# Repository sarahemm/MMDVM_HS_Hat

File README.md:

# MMDVM_HS_Hat
MMDVM_HS Hat for the Raspberry Pi (Zero)

This project provides a Raspberry Pi Hat for the [MMDVM_HS Hotspot](https://github.com/juribeparada/MMDVM_HS). It was designed for the Raspberry Pi Zero, but should work on any other Pi with the Hat interface. 

First revisions of the board have been built successfully!

The PCB is designed in KiCad and the necessary libraries are included. The supplied Gerber files can be used to order PCBs, for example at Elecrow or DirtyPCBs. The board's dimensions are 65x30mm.

You can order 3 beautiful, purple Revision 1.2 PCBs for $15 at [OSHPark](https://oshpark.com/shared_projects/WaiMw5XE)! 

## 3D printed Case

Thanks to Toufik, F0DEI we added the sources for a shiny case that you can print with your 3D printer. It may require a little upscaling depending on your printer model. It can carry a Raspberry Pi Zero (W) with MMDVM_HS_Hat (SMA) on top.

## Revisions
### Revision 0
This was the first released version that still contains a couple of errors. There is a trace missing between L1 and C1 that needs to be fixed with a small blob of solder or magnet wire. Otherwise the RF connector is not connected to the ADF7021. The GND side of C20 and C22 is not connected to the rest of the board's GND, this needs to be fixed with a little wire to any other GND. CE is connected directly to +3.3V which disallows mode scanning to work. If you just use one mode this is fine, otherwise the connection to the CE pin has to be cut and connected to PC14 on the STM32.

Earlier schematics showed C14 as 1uF. This is wrong and needs to be replaced with 1nF, otherwise the ADF7021 will neither receive nor transmit properly.

With these changes, you can build a fully working MMDVM_HS with the old revision 0 boards

### Revision 1
These boards have "Revision 1" written on them. All bugs found in revision 0 are fixed in this version. Apart from that, the STM32's BOOT0 and RESET pins are connected to GPIOs of the Raspberry Pi. This way, flashing should be possible without manually jumpering BOOT0 and triggering a reset.

Component placement did not change between revisions 0 and 1, therefore any stencils for revision 0 should work for revision 1 boards, too.

### Revision 1.1
Rewired 3v3 line for Nextion display connector to 5v0. Added SERVICE LED for visual heartbeat. Fixed improper labelling on P25 and YSF LEDs. Due to added LEDs this revision requires a new stencil.

### Revision 1.2
This Revision adds support for an optional AN1603-443 ceramic antenna. Insert C27 or C28, depending on what kind of antenna you want to use.

### Revision 1.3
The boot jumper was removed and the STlink header moved to its position. This gave space for another 4-pin header allowing to connect I²C OLED displays. No new stencil needed

### Revision 1.4
The SVC LED has been rotated and thus aligned to the layout of all other LEDs. The RainSun ceramic antenna has been replaced by a model that can be ordered at Mouser. DC line filtering has been added to 3v3 line.

### Revision 1.5
A fith mode LED has been added to the board to show NXDN activity. The two pin headers moved downwards a little. The rev1.4 stencil can be re-used if you manually add solder paste to R19 and D9 afterwards.

### Revision 1.6
Inner RX/TX pins of Nextion connector have been swapped. External VCO inductor L6 was added. This is optional for VHF use. D-Star and DMR LEDs were swapped to flash LEDs in proper scan order :).

### Revision 1.6a - sen
Updated for KiCad 9 footprints, as well as some silkscreen changes. No BOM changes, so standard 1.6 BOM applies.Previous versions of stencils won't work well with this one due to footprint shapes changing and some slight component location nudges.

## BOM
* All necessary parts for the Revision 1.1 board can be ordered at Mouser using the following [shopping cart](http://www.mouser.com/ProjectManager/ProjectDetail.aspx?AccessID=780b8eac44)
* All necessary parts for the Revision 1.2 board can be ordered at Mouser using the following [shopping cart](http://www.mouser.com/ProjectManager/ProjectDetail.aspx?AccessID=035e777242)
* There is also a light version of revision 1.2 without the reset switch, 2.54mm headers and SMA connector [Link](http://www.mouser.com/ProjectManager/ProjectDetail.aspx?AccessID=3f7d0256e1)
* The parts for Revision 1.3 board are in this [Mouser cart](http://www.mouser.com/ProjectManager/ProjectDetail.aspx?AccessID=250d76339b) and the light version is [here](http://www.mouser.com/ProjectManager/ProjectDetail.aspx?AccessID=2d533ac53d)
* [Mouser project](http://www.mouser.com/ProjectManager/ProjectDetail.aspx?AccessID=5cab954f40) for MMDVM_HS_Hat revision 1.4
* There is another [Mouser cart for rev 1.5](https://www.mouser.com/ProjectManager/ProjectDetail.aspx?AccessID=5a3e4ae018).
* And this is the [rev1.6 cart](https://www.mouser.com/ProjectManager/ProjectDetail.aspx?AccessID=48302f4221) and its [light version](https://www.mouser.com/ProjectManager/ProjectDetail.aspx?AccessID=ac888de33a).

Please note that the onboard ceramic antenna is not supplied by Mouser and therefore missing in the carts for revisions up to 1.3.

Either the ADF7021 or the ADF7021-N can be used. Define the proper version in the firmware!

## Firmware Installation

### Compile and upload manually

For specific details about the firmware installation, check [these](https://github.com/juribeparada/MMDVM_HS#build-de-firmware-and-upload-to-zumspot-rpi) instructions. The process is similar to the installation on the ZumSpot Pi. 

Enable the following settings in Config.h:

    #define MMDVM_HS_HAT_REV12
    #define ENABLE_ADF7021
    #define ADF7021_14_7456
    #define STM32_USART1_HOST
    #define ENABLE_SCAN_MODE

Build the firmware:

    make

And finally upload the firmware to the MMDVM_HS_Hat:

    sudo make mmdvm_hs_hat

### Update within Pi-Star

Andy, MW0MWZ was so kind as to add a script which allows for updating the firmware of the MMDVM_HS_Hat within the running Pi-Star system. It uses the pre-compiled binaries from Andy's (CA6JAU) github repository. The update can be done with:

```
$ pistar-zumspotflash hs_hat
```

on the command line.

## Accessoires

* A case for the #MMDVM_HS_Hat can be found at amazon: [Case](https://www.amazon.de/Hochwertiges-schwarzes-auml-uuml-Raspberry/dp/B01FHDXNNU)

* An OLED display also to be found at amazon: [Display](https://www.amazon.de/dp/B01M9JVYIS/ref=cm_sw_r_wa_api_RmZ9zb01APZTV)

## License
This project is released under the Creative Commons Attribution-NonCommercial-ShareAlike 3.0 (CC-BY-NC-SA 3.0, https://creativecommons.org/licenses/by-nc-sa/3.0/) license. You may edit and share it as you like, as long as credit is given and the license is not changed. You can build as many boards for you and your friends as you like and you can even sell it to them to cover your costs, **however it is strictly forbidden to turn this into a commercial product! You are not allowed to build and sell these boards for profit!**

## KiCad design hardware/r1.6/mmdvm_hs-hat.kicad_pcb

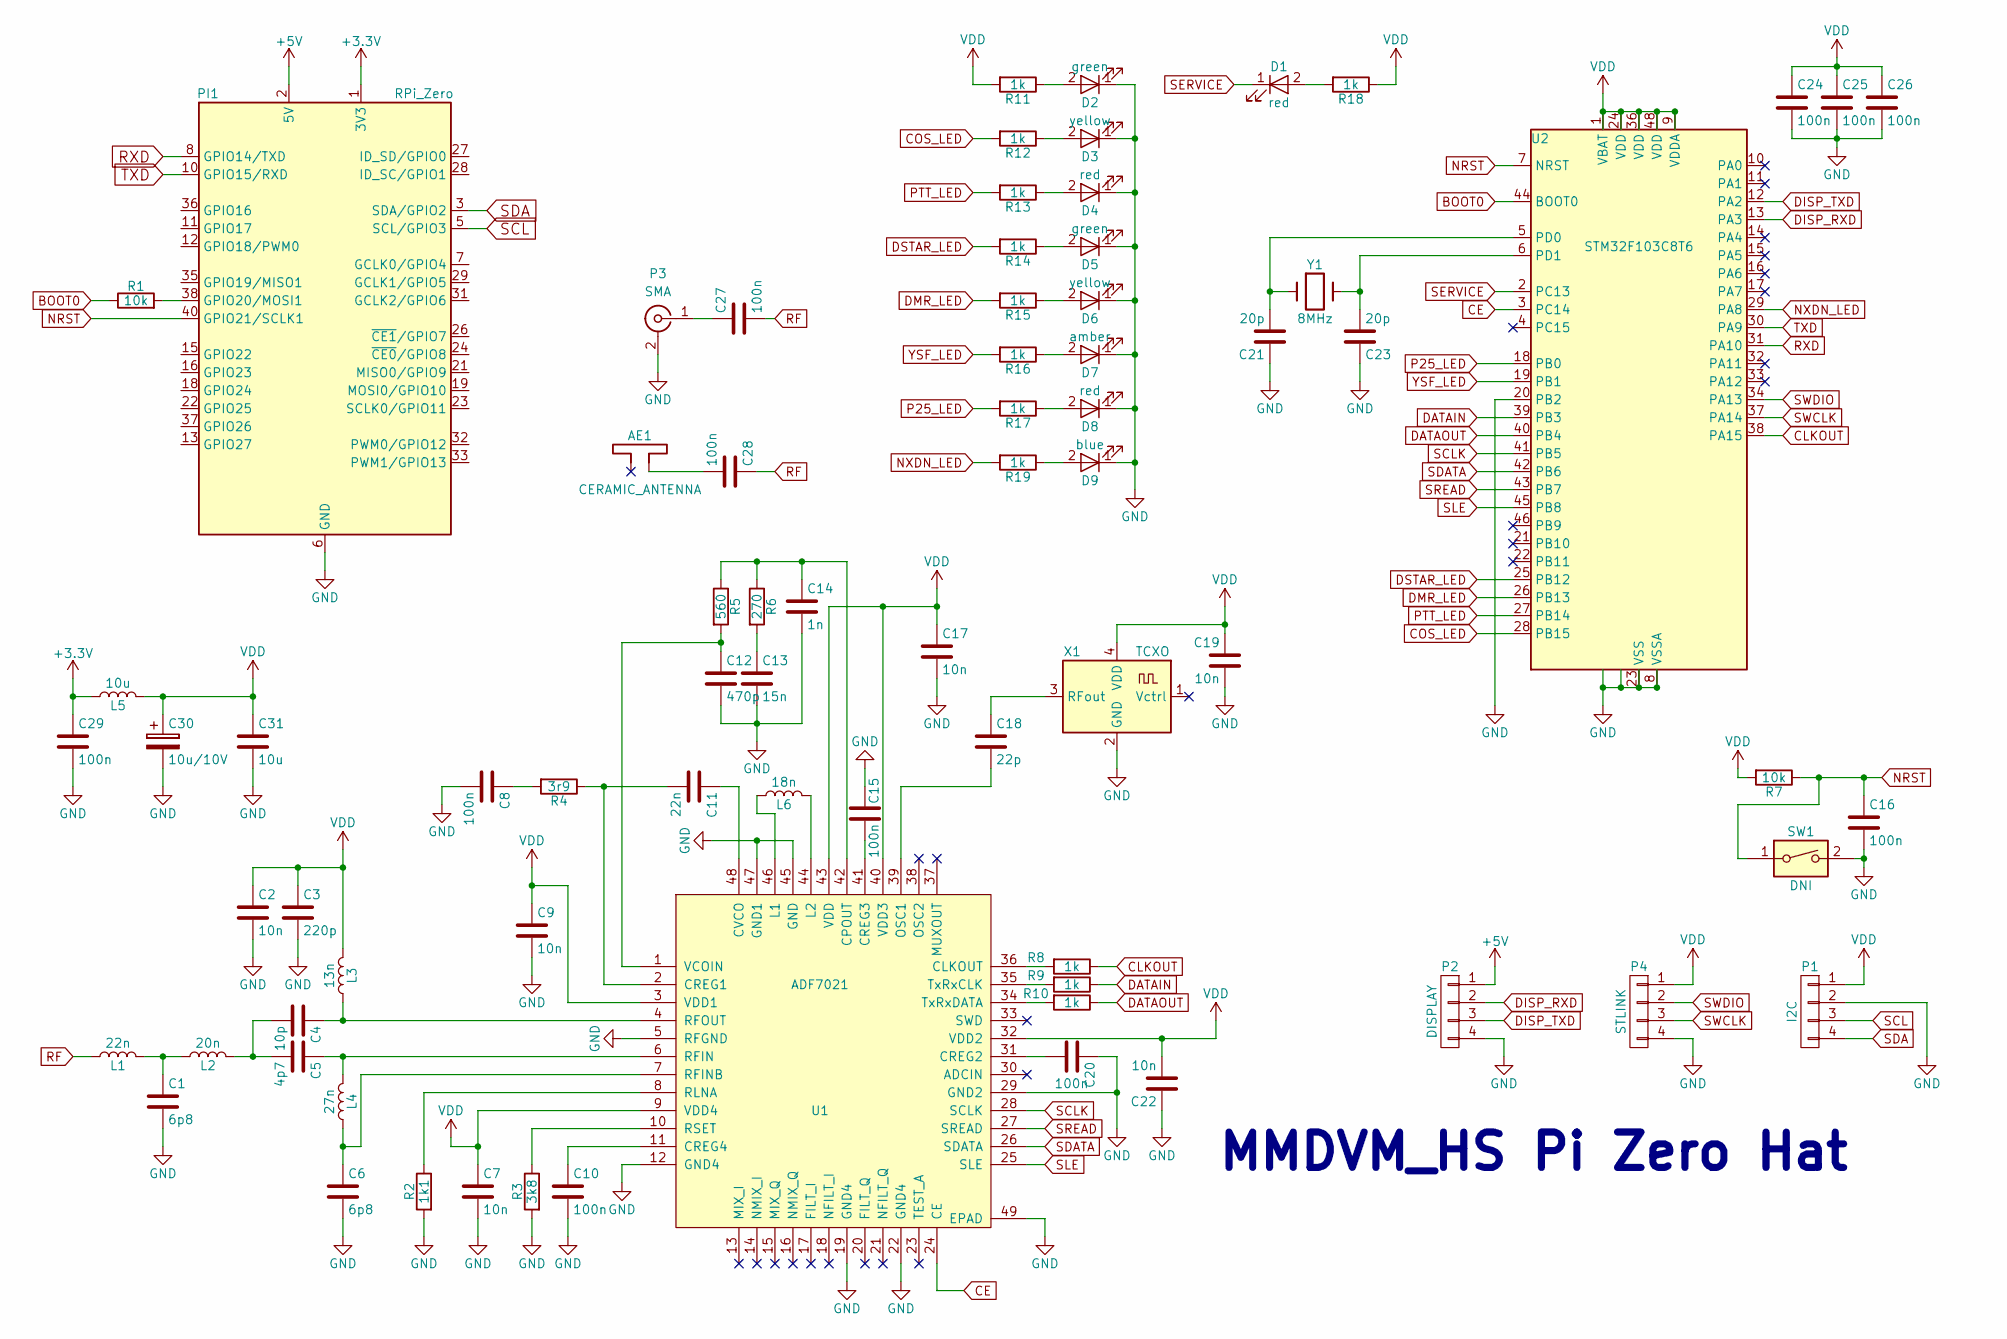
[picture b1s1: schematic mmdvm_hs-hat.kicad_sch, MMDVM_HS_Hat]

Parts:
AE1: CERAMIC_ANTENNA; ANT1204; MPN ANT1204F002R0433A
C1, C6: 6p8; C_0402_1005Metric; MPN GJM1555C1H6R8BB01D
C2, C7, C9, C17, C19, C22: 10n; C_0402_1005Metric; MPN VJ0402Y103KXJCW1BC
C3: 220p; C_0402_1005Metric; MPN GRM1555C1H221JA01D
C4: 10p; C_0402_1005Metric; MPN GRM1555C1E100GA01D
C5: 4p7; C_0402_1005Metric; MPN GRM1555C1H4R7CA01D
C8, C10, C15, C16, C20, C24, C25, C26, C27, C28, C29: 100n; C_0402_1005Metric; MPN VJ0402V104ZXJCW1BC
C11: 22n; C_0402_1005Metric; MPN GCM155R71E223KA55D
C12: 470p; C_0402_1005Metric; MPN GRM155R71H471KA01D
C13: 15n; C_0402_1005Metric; MPN GRM155R71C153KA01D
C14: 1n; C_0402_1005Metric; MPN GRM155R60J102KA01D
C18: 22p; C_0402_1005Metric; MPN 04025A220GAT2A
C21, C23: 20p; C_0402_1005Metric; MPN GJM1555C1H200FB01D
C30: 10u/10V; CP_EIA-3216-18_Kemet-A; MPN F931A106KAA
C31: 10u; C_0402_1005Metric; MPN GRJ155R60J106ME11D
D1, D4, D8: red; LED_0402_1005Metric; MPN APHHS1005SURCK
D2: green; LED_0402_1005Metric; MPN APHHS1005CGCK
D3: yellow; LED_0402_1005Metric; MPN APG1005SYC-T
D5: green; LED_0402_1005Metric; MPN APG1005SYC-T
D6: yellow; LED_0402_1005Metric; MPN APHHS1005CGCK
D7: amber; LED_0402_1005Metric; MPN APG1005SEC-T
D9: blue; LED_0402_1005Metric; MPN APHHS1005QBC/D
L1: 22n; L_0402_1005Metric; MPN LQW15CA22NJ00D
L2: 20n; L_0402_1005Metric; MPN 36501E20NJTDG
L3: 13n; L_0402_1005Metric; MPN LQW15AN13NG80D
L4: 27n; L_0402_1005Metric; MPN LQW15AN27NG80D
L5: 10u; L_0402_1005Metric; MPN 74279277
L6: 18n; L_0402_1005Metric; MPN 36501E18NJTDG
P1: I2C; PinHeader_1x04_P2.54mm_Vertical; MPN 826629-4
P2: DISPLAY; PinHeader_1x04_P2.54mm_Vertical; MPN 826629-4
P3: SMA; SMA_Amphenol_901-144_Vertical
P4: STLINK; PinHeader_1x04_P2.54mm_Vertical; MPN 826629-4
PI1: RPi_Zero
R1, R7: 10k; R_0402_1005Metric; MPN CRCW040210K0FKED
R2: 1k1; R_0402_1005Metric; MPN RR0510P-112-D
R3: 3k8; R_0402_1005Metric; MPN RR0510P-3831-D
R4: 3r9; R_0402_1005Metric; MPN CRCW04023R90JNED
R5: 560; R_0402_1005Metric; MPN ERA-2AEB561X
R6: 270; R_0402_1005Metric; MPN ERA-2AEB271X
R8, R9, R10, R11, R12, R13, R14, R15, R16, R17, R18, R19: 1k; R_0402_1005Metric; MPN ERJ-PA2D1001X
SW1: DNI; SW_SPST_B3U-1000P; MPN B3U-1000P
U1: ADF7021; QFN-48-1EP_7x7mm_P0.5mm_EP5.1x5.1mm; MPN ADF7021BCPZ
U2: STM32F103C8T6; LQFP-48_7x7mm_P0.5mm
X1: TCXO; Crystal_SMD_3225-4Pin_3.2x2.5mm
Y1: 8MHz; Crystal_SMD_Abracon_ABM3-2Pin_5.0x3.2mm; MPN ABM3-8.000MHz-D2Y-T

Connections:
+3.3V: C29.1, L5.1, PI1.1 (3V3), PI1.17 (3V3)
+5V: P2.1, PI1.2 (5V), PI1.4 (5V)
BOOT0: R1.1, U2.44 (BOOT0)
CE: U1.24 (CE), U2.3 (PC14)
CLKOUT: R8.1, U2.38 (PA15)
COS_LED: R12.2, U2.28 (PB15)
DATAIN: R9.1, U2.39 (PB3)
DATAOUT: R10.1, U2.40 (PB4)
DISP_RXD: P2.2, U2.13 (PA3)
DISP_TXD: P2.3, U2.12 (PA2)
DMR_LED: R15.2, U2.26 (PB13)
DSTAR_LED: R14.2, U2.25 (PB12)
GND: C1.2, C2.2, C3.2, C6.2, C7.2, C8.2, C9.2, C10.2, C12.2, C13.2, C14.2, C15.1, C16.2, C17.2, C19.2, C20.1, C21.1, C22.1, C23.1, C24.2, C25.2, C26.2, C29.2, C30.2, C31.2, D2.1 (K), D3.1 (K), D4.1 (K), D5.1 (K), D6.1 (K), D7.1 (K), D8.1 (K), D9.1 (K), P1.2, P2.4, P3.2 (Ext), P4.4, PI1.6 (GND), PI1.9 (GND), PI1.14 (GND), PI1.20 (GND), PI1.25 (GND), PI1.30 (GND), PI1.34 (GND), PI1.39 (GND), R2.2, R3.2, SW1.2, U1.5 (RFGND), U1.12 (GND4), U1.19 (GND4), U1.22 (GND4), U1.29 (GND2), U1.45 (GND), U1.47 (GND1), U1.49 (EPAD), U2.8 (VSSA), U2.20 (PB2), U2.23 (VSS), U2.35 (VSS), U2.47 (VSS), X1.2 (GND)
NRST: C16.1, PI1.40 (GPIO21/SCLK1), R7.1, SW1.1, U2.7 (NRST)
NXDN_LED: R19.2, U2.29 (PA8)
unnamed: AE1.1, C28.2
unnamed: C1.1, L1.2, L2.1
unnamed: C4.2, C5.2, L2.2
unnamed: C8.1, R4.2
unnamed: C13.1, R6.2
unnamed: D1.2 (A), R18.2
unnamed: D2.2 (A), R11.1
unnamed: D3.2 (A), R12.1
unnamed: D4.2 (A), R13.1
unnamed: D5.2 (A), R14.1
unnamed: D6.2 (A), R15.1
unnamed: D7.2 (A), R16.1
unnamed: D8.2 (A), R17.1
unnamed: D9.2 (A), R19.1
unnamed: C27.1, P3.1 (In)
unnamed: PI1.38 (GPIO20/MOSI1), R1.2
unnamed: R8.2, U1.36 (CLKOUT)
unnamed: C14.1, R5.1, R6.1, U1.42 (CPOUT)
unnamed: C11.2, R4.1, U1.2 (CREG1)
unnamed: C20.2, U1.31 (CREG2)
unnamed: C15.2, U1.41 (CREG3)
unnamed: C10.1, U1.11 (CREG4)
unnamed: C11.1, U1.48 (CVCO)
unnamed: L6.1, U1.46 (L1)
unnamed: L6.2, U1.44 (L2)
unnamed: C18.2, U1.39 (OSC1)
unnamed: C5.1, L4.2, U1.6 (RFIN)
unnamed: C6.1, L4.1, U1.7 (RFINB)
unnamed: C4.1, L3.1, U1.4 (RFOUT)
unnamed: R2.1, U1.8 (RLNA)
unnamed: R3.1, U1.10 (RSET)
unnamed: R9.2, U1.35 (TxRxCLK)
unnamed: R10.2, U1.34 (TxRxDATA)
unnamed: C12.1, R5.2, U1.1 (VCOIN)
unnamed: C21.2, U2.5 (PD0), Y1.1
unnamed: C23.2, U2.6 (PD1), Y1.2
unnamed: C18.1, X1.3 (RFout)
P25_LED: R17.2, U2.18 (PB0)
PTT_LED: R13.2, U2.27 (PB14)
RF: C27.2, C28.1, L1.1
RXD: PI1.8 (GPIO14/TXD), U2.31 (PA10)
SCL: P1.3, PI1.5 (SCL/GPIO3)
SCLK: U1.28 (SCLK), U2.41 (PB5)
SDA: P1.4, PI1.3 (SDA/GPIO2)
SDATA: U1.26 (SDATA), U2.42 (PB6)
SERVICE: D1.1 (K), U2.2 (PC13)
SLE: U1.25 (SLE), U2.45 (PB8)
SREAD: U1.27 (SREAD), U2.43 (PB7)
SWCLK: P4.3, U2.37 (PA14)
SWDIO: P4.2, U2.34 (PA13)
TXD: PI1.10 (GPIO15/RXD), U2.30 (PA9)
VDD: C2.1, C3.1, C7.1, C9.1, C17.1, C19.1, C22.2, C24.1, C25.1, C26.1, C30.1, C31.1, L3.2, L5.2, P1.1, P4.1, R7.2, R11.2, R18.1, U1.3 (VDD1), U1.9 (VDD4), U1.32 (VDD2), U1.40 (VDD3), U1.43 (VDD), U2.1 (VBAT), U2.9 (VDDA), U2.24 (VDD), U2.36 (VDD), U2.48 (VDD), X1.4 (VDD)
YSF_LED: R16.2, U2.19 (PB1)

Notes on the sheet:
MMDVM_HS Pi Zero Hat

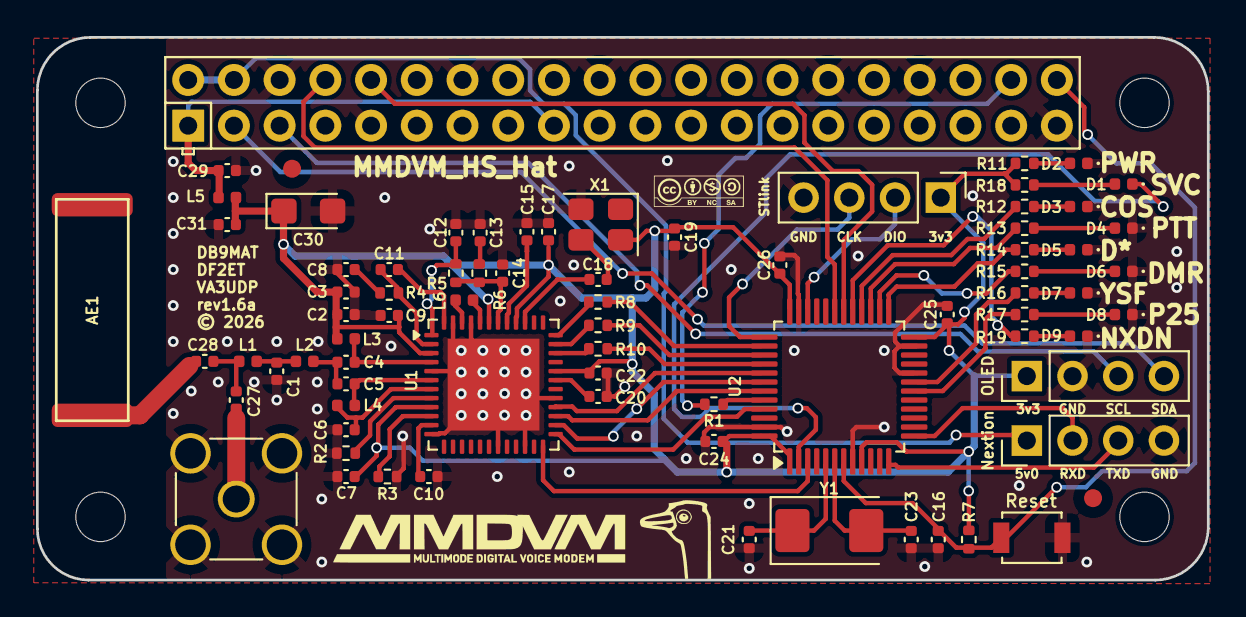
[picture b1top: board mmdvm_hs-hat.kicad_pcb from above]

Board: 2 copper layers, 65.1 x 30.2 mm, 76 parts (0 on the bottom side), 68 nets.

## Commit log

2026-02-14 Updated sch/proj to KiCad 9 and light cleanup
2026-02-14 Updated PCB for KiCad 9
    Includes new footprints etc. All DRC issues now cleaned up.
2026-02-14 Updated copyright and fixed some 3D stuff
2026-02-14 Bumped text size up sligthly
    This will help with legibility at some board houses. Also added my ostrich, box for serial number, and a couple other minor silkscreen changes.
2026-02-14 Added note about 1.6 BOM and fixed image URL
2026-02-14 Updated image to reflect PCB changes
2026-02-16 Remove gerbers from gitignore and add to repo
    These are output for JLCPCB.

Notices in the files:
hardware/r1.6/mmdvm_hs-hat.kicad_pcb:
© 2026
